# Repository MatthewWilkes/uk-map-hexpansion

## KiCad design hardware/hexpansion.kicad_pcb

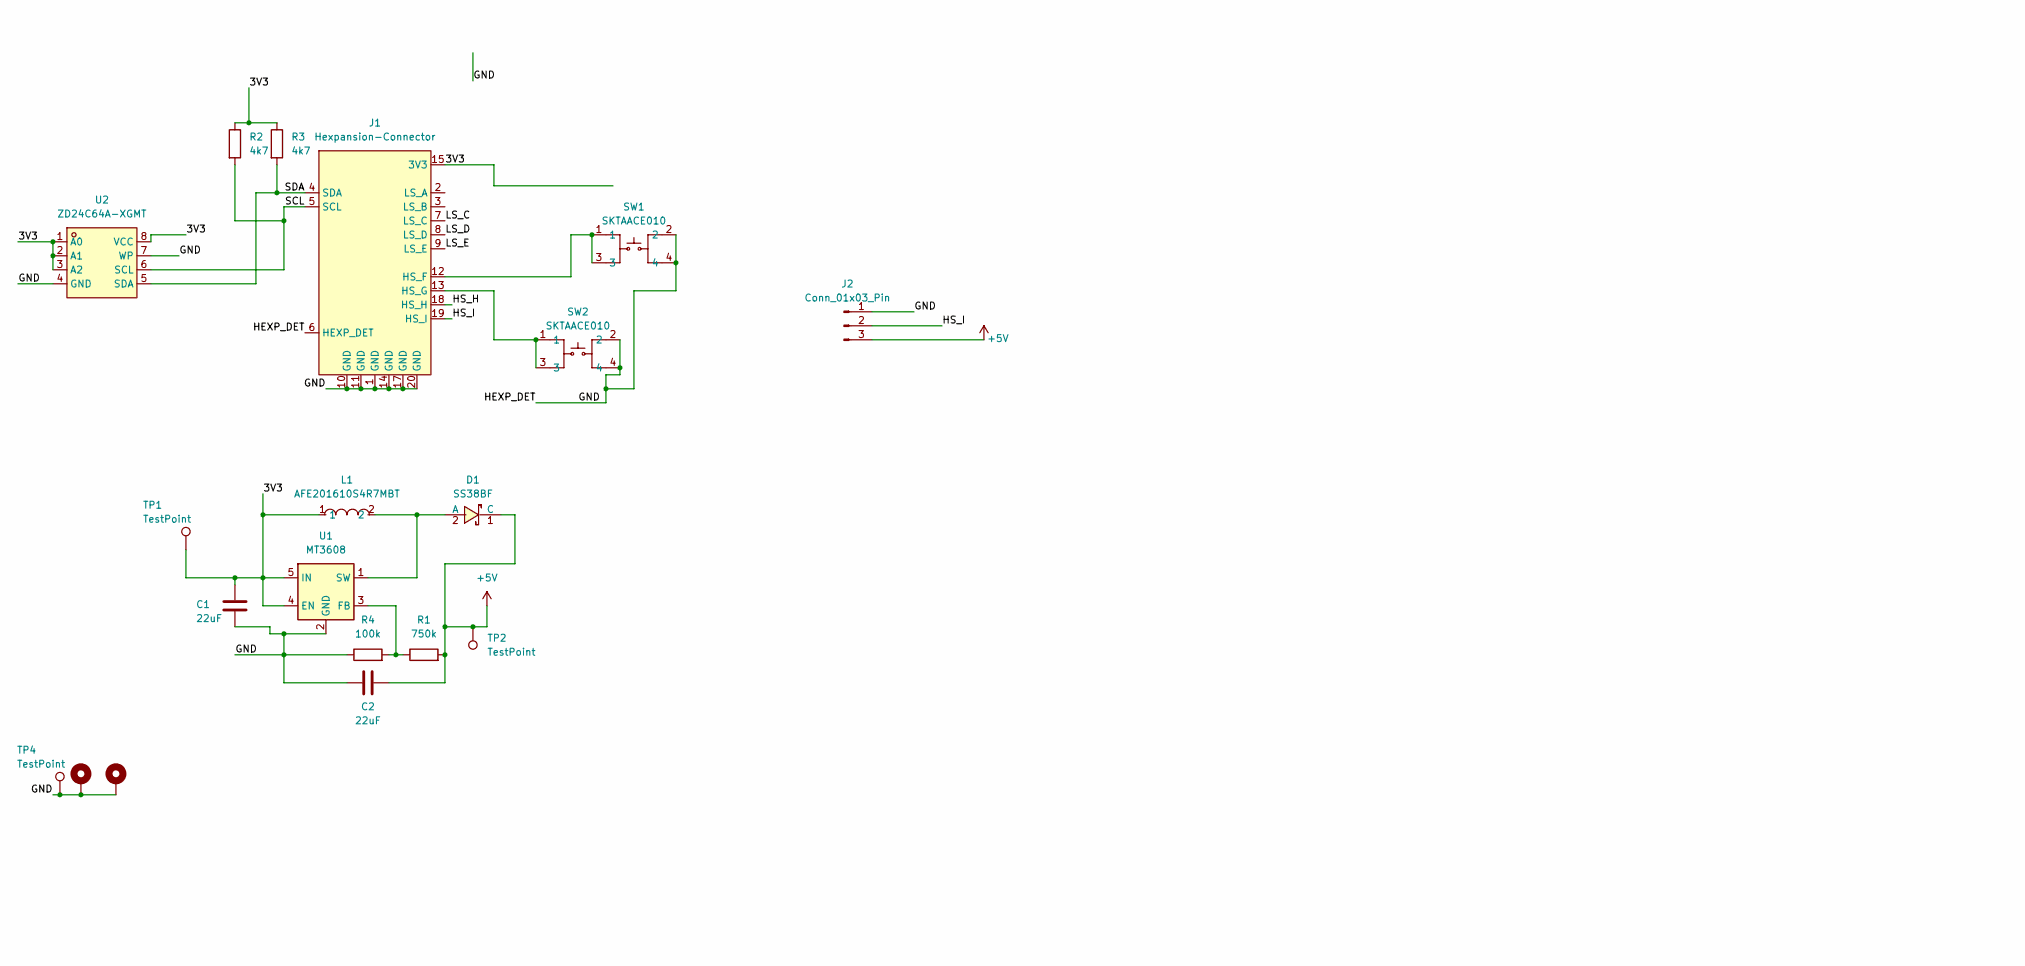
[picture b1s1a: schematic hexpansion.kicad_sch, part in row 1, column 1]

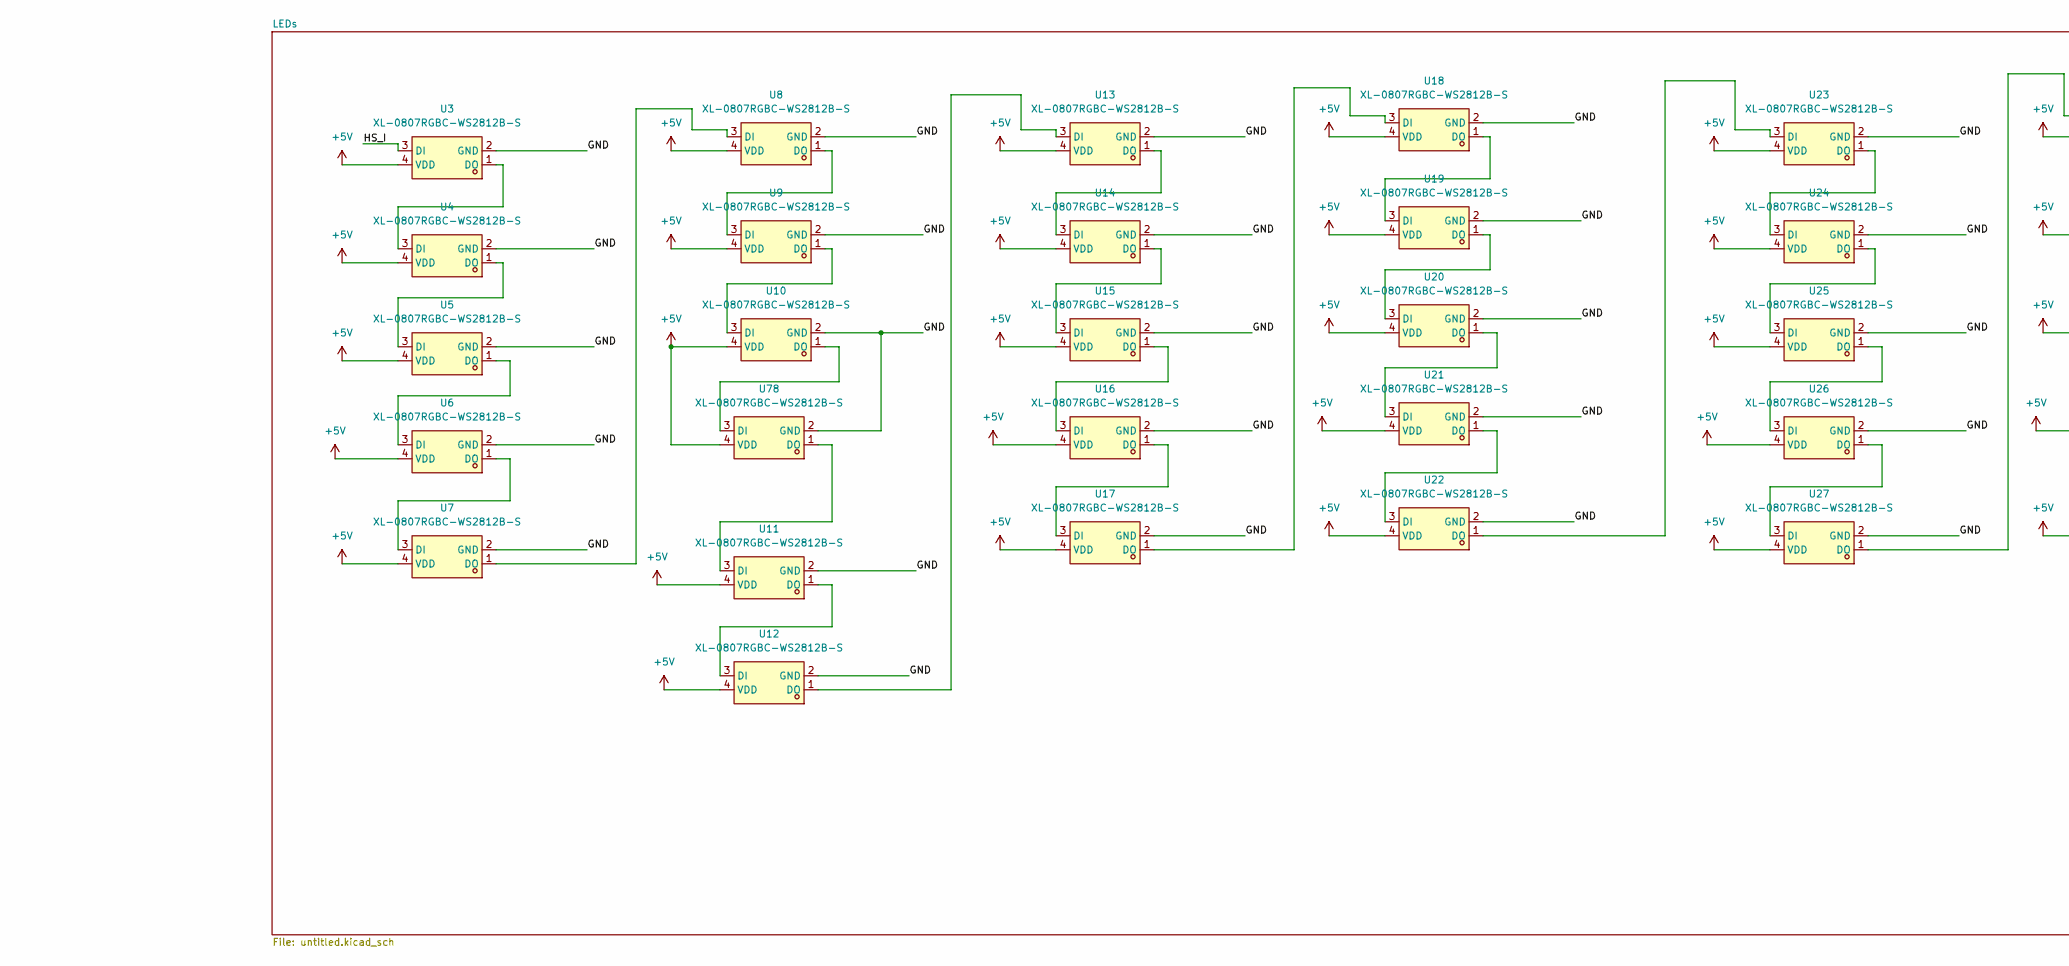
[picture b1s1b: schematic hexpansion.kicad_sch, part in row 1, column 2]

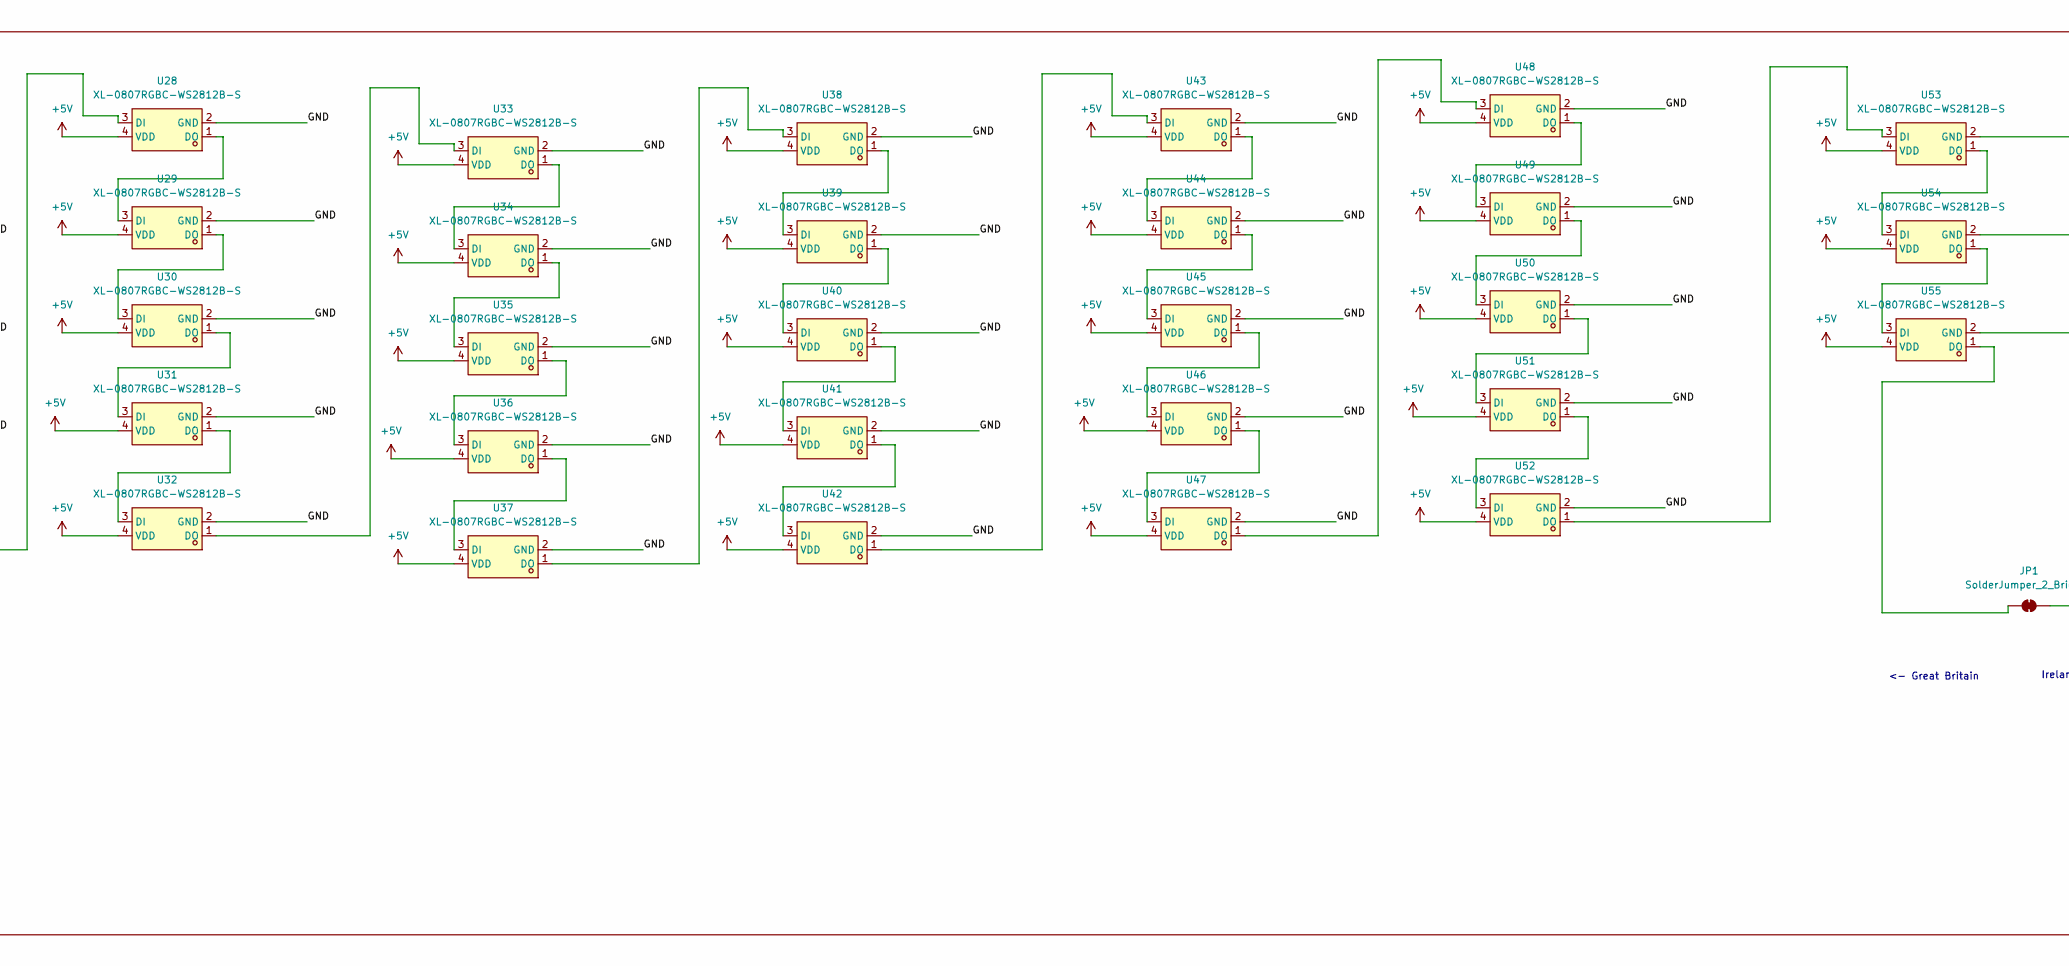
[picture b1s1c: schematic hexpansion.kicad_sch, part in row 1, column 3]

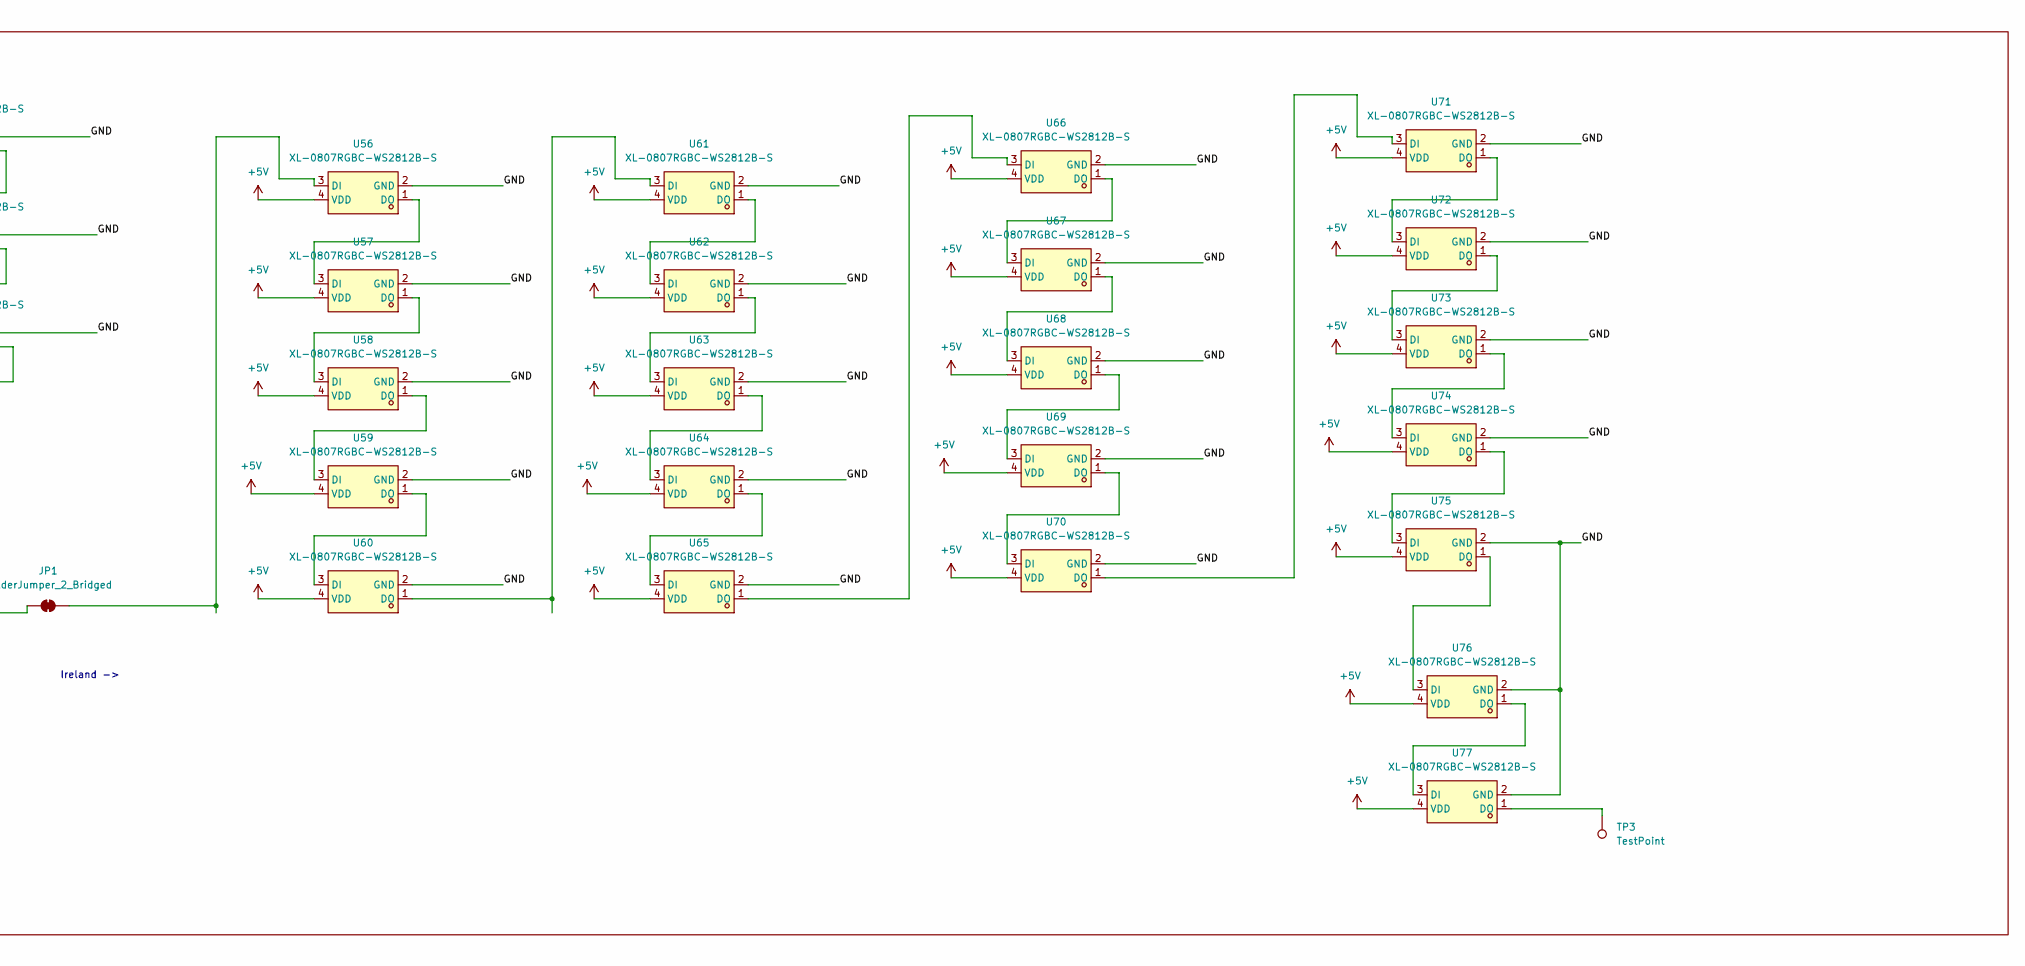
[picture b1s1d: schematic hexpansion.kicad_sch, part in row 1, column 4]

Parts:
C1, C2: 22uF; C_0603_1608Metric; LCSC Part C86295
D1: SS38BF; SMBF_L4.3-W3.6-LS5.3-RD; MPN SS38BF; LCSC Part C437976
H1, H2: MountingHole_Pad; MountingHole_2.2mm_M2_Pad_Via
J1: Hexpansion-Connector; hexpansion-edge-connector
J2: Conn_01x03_Pin; SolderWire-0.1sqmm_1x03_P3.6mm_D0.4mm_OD1mm
JP1: SolderJumper_2_Bridged; SolderJumper-2_P1.3mm_Bridged_RoundedPad1.0x1.5mm
L1: AFE201610S4R7MBT; IND-SMD_L2.0-W1.6; MPN AFE201610S4R7MBT; LCSC Part C22459317
R1: 750k; R_0603_1608Metric; LCSC Part C137684
R2, R3: 4k7; R_0603_1608Metric
R4: 100k; R_0603_1608Metric; LCSC Part C14675
SW1, SW2: SKTAACE010; KEY-SMD_4P-L2.6-W1.6-P0.80-LS3.0; MPN SKTAACE010; LCSC Part C358621
TP1, TP2, TP3, TP4: TestPoint; TestPoint_Pad_2.0x2.0mm
U1: MT3608; SOT-23-6; LCSC Part C84817
U2: ZD24C64A-XGMT; TSSOP-8_L4.4-W3.0-P0.65-LS6.4-BL; LCSC Part C2875852
U3, U4, U5, U6, U7, U8, U9, U10, U11, U12, U13, U14, U15, U16, U17, U18, U19, U20, U21, U22, U23, U24, U25, U26, U27, U28, U29, U30, U31, U32, U33, U34, U35, U36, U37, U38, U39, U40, U41, U42, U43, U44, U45, U46, U47, U48, U49, U50, U51, U52, U53, U54, U55, U56, U57, U58, U59, U60, U61, U62, U63, U64, U65, U66, U67, U68, U69, U70, U71, U72, U73, U74, U75, U76, U77, U78: XL-0807RGBC-WS2812B-S; LED-SMD_4P-L2.0-W1.8_XL-0807RGBC-WS2812B-S; LCSC Part C41413181

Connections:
+5V: C2.2, D1.1 (C), J2.3, R1.2, TP2.1, U3.4 (VDD), U4.4 (VDD), U5.4 (VDD), U6.4 (VDD), U7.4 (VDD), U8.4 (VDD), U9.4 (VDD), U10.4 (VDD), U11.4 (VDD), U12.4 (VDD), U13.4 (VDD), U14.4 (VDD), U15.4 (VDD), U16.4 (VDD), U17.4 (VDD), U18.4 (VDD), U19.4 (VDD), U20.4 (VDD), U21.4 (VDD), U22.4 (VDD), U23.4 (VDD), U24.4 (VDD), U25.4 (VDD), U26.4 (VDD), U27.4 (VDD), U28.4 (VDD), U29.4 (VDD), U30.4 (VDD), U31.4 (VDD), U32.4 (VDD), U33.4 (VDD), U34.4 (VDD), U35.4 (VDD), U36.4 (VDD), U37.4 (VDD), U38.4 (VDD), U39.4 (VDD), U40.4 (VDD), U41.4 (VDD), U42.4 (VDD), U43.4 (VDD), U44.4 (VDD), U45.4 (VDD), U46.4 (VDD), U47.4 (VDD), U48.4 (VDD), U49.4 (VDD), U50.4 (VDD), U51.4 (VDD), U52.4 (VDD), U53.4 (VDD), U54.4 (VDD), U55.4 (VDD), U56.4 (VDD), U57.4 (VDD), U58.4 (VDD), U59.4 (VDD), U60.4 (VDD), U61.4 (VDD), U62.4 (VDD), U63.4 (VDD), U64.4 (VDD), U65.4 (VDD), U66.4 (VDD), U67.4 (VDD), U68.4 (VDD), U69.4 (VDD), U70.4 (VDD), U71.4 (VDD), U72.4 (VDD), U73.4 (VDD), U74.4 (VDD), U75.4 (VDD), U76.4 (VDD), U77.4 (VDD), U78.4 (VDD); also elsewhere on the board
/3V3: C1.1, J1.15 (3V3), J1.16 (3V3), L1.1, R2.1, R3.1, TP1.1, U1.4 (EN), U1.5 (IN), U2.1 (A0), U2.2 (A1), U2.3 (A2), U2.8 (VCC); also elsewhere on the board
/GND: C1.2, C2.1, H1.1, H2.1, J1.1 (GND), J1.6 (HEXP_DET), J1.10 (GND), J1.11 (GND), J1.14 (GND), J1.17 (GND), J1.20 (GND), J2.1, R4.1, SW1.2, SW1.4, SW2.2, SW2.4, TP4.1, U1.2 (GND), U2.4 (GND), U2.7 (WP), U3.2 (GND), U4.2 (GND), U5.2 (GND), U6.2 (GND), U7.2 (GND), U8.2 (GND), U9.2 (GND), U10.2 (GND), U11.2 (GND), U12.2 (GND), U13.2 (GND), U14.2 (GND), U15.2 (GND), U16.2 (GND), U17.2 (GND), U18.2 (GND), U19.2 (GND), U20.2 (GND), U21.2 (GND), U22.2 (GND), U23.2 (GND), U24.2 (GND), U25.2 (GND), U26.2 (GND), U27.2 (GND), U28.2 (GND), U29.2 (GND), U30.2 (GND), U31.2 (GND), U32.2 (GND), U33.2 (GND), U34.2 (GND), U35.2 (GND), U36.2 (GND), U37.2 (GND), U38.2 (GND), U39.2 (GND), U40.2 (GND), U41.2 (GND), U42.2 (GND), U43.2 (GND), U44.2 (GND), U45.2 (GND), U46.2 (GND), U47.2 (GND), U48.2 (GND), U49.2 (GND), U50.2 (GND), U51.2 (GND), U52.2 (GND), U53.2 (GND), U54.2 (GND), U55.2 (GND), U56.2 (GND), U57.2 (GND), U58.2 (GND), U59.2 (GND), U60.2 (GND), U61.2 (GND), U62.2 (GND), U63.2 (GND), U64.2 (GND), U65.2 (GND), U66.2 (GND), U67.2 (GND), U68.2 (GND), U69.2 (GND), U70.2 (GND), U71.2 (GND), U72.2 (GND), U73.2 (GND), U74.2 (GND), U75.2 (GND), U76.2 (GND), U77.2 (GND), U78.2 (GND); also elsewhere on the board
/HS_H: J1.18 (HS_H)
/HS_I: J1.19 (HS_I), J2.2, U3.3 (DI); also elsewhere on the board
/LS_C: J1.7 (LS_C)
/LS_D: J1.8 (LS_D)
/LS_E: J1.9 (LS_E)
/SCL: J1.5 (SCL), R2.2, U2.6 (SCL)
/SDA: J1.4 (SDA), R3.2, U2.5 (SDA)
unnamed: D1.2 (A), L1.2, U1.1 (SW)
unnamed 11: J1.12 (HS_F), SW1.1, SW1.3; also elsewhere on the board
unnamed 12: J1.13 (HS_G), SW2.1, SW2.3; also elsewhere on the board
unnamed 13: JP1.1 (A), U55.1 (DO); also elsewhere on the board
unnamed 14: JP1.2 (B), U56.3 (DI); also elsewhere on the board
unnamed: R1.1, R4.2, U1.3 (FB)
unnamed: U3.1 (DO), U4.3 (DI)
unnamed: U4.1 (DO), U5.3 (DI)
unnamed: U5.1 (DO), U6.3 (DI)
unnamed: U6.1 (DO), U7.3 (DI)
unnamed: U7.1 (DO), U8.3 (DI)
unnamed: U8.1 (DO), U9.3 (DI)
unnamed: U9.1 (DO), U10.3 (DI)
unnamed: U10.1 (DO), U78.3 (DI)
unnamed: U11.3 (DI), U78.1 (DO)
unnamed: U11.1 (DO), U12.3 (DI)
unnamed: U12.1 (DO), U13.3 (DI)
unnamed: U13.1 (DO), U14.3 (DI)
unnamed: U14.1 (DO), U15.3 (DI)
unnamed: U15.1 (DO), U16.3 (DI)
unnamed: U16.1 (DO), U17.3 (DI)
unnamed: U17.1 (DO), U18.3 (DI)
unnamed: U18.1 (DO), U19.3 (DI)
unnamed: U19.1 (DO), U20.3 (DI)
unnamed: U20.1 (DO), U21.3 (DI)
unnamed: U21.1 (DO), U22.3 (DI)
unnamed: U22.1 (DO), U23.3 (DI)
unnamed: U23.1 (DO), U24.3 (DI)
unnamed: U24.1 (DO), U25.3 (DI)
unnamed: U25.1 (DO), U26.3 (DI)
unnamed: U26.1 (DO), U27.3 (DI)
unnamed: U27.1 (DO), U28.3 (DI)
unnamed: U28.1 (DO), U29.3 (DI)
unnamed: U29.1 (DO), U30.3 (DI)
unnamed: U30.1 (DO), U31.3 (DI)
unnamed: U31.1 (DO), U32.3 (DI)
unnamed: U32.1 (DO), U33.3 (DI)
unnamed: U33.1 (DO), U34.3 (DI)
unnamed: U34.1 (DO), U35.3 (DI)
unnamed: U35.1 (DO), U36.3 (DI)
unnamed: U36.1 (DO), U37.3 (DI)
unnamed: U37.1 (DO), U38.3 (DI)
unnamed: U38.1 (DO), U39.3 (DI)
unnamed: U39.1 (DO), U40.3 (DI)
unnamed: U40.1 (DO), U41.3 (DI)
unnamed: U41.1 (DO), U42.3 (DI)
unnamed: U42.1 (DO), U43.3 (DI)
unnamed: U43.1 (DO), U44.3 (DI)
unnamed: U44.1 (DO), U45.3 (DI)
unnamed: U45.1 (DO), U46.3 (DI)
unnamed: U46.1 (DO), U47.3 (DI)
unnamed: U47.1 (DO), U48.3 (DI)
unnamed: U48.1 (DO), U49.3 (DI)
unnamed: U49.1 (DO), U50.3 (DI)
unnamed: U50.1 (DO), U51.3 (DI)
unnamed: U51.1 (DO), U52.3 (DI)
unnamed: U52.1 (DO), U53.3 (DI)
unnamed: U53.1 (DO), U54.3 (DI)
unnamed: U54.1 (DO), U55.3 (DI)
unnamed: U56.1 (DO), U57.3 (DI)
unnamed: U57.1 (DO), U58.3 (DI)
unnamed: U58.1 (DO), U59.3 (DI)
unnamed: U59.1 (DO), U60.3 (DI)
unnamed: U60.1 (DO), U61.3 (DI)
unnamed: U61.1 (DO), U62.3 (DI)
unnamed: U62.1 (DO), U63.3 (DI)
unnamed: U63.1 (DO), U64.3 (DI)
unnamed: U64.1 (DO), U65.3 (DI)
unnamed: U65.1 (DO), U66.3 (DI)
unnamed: U66.1 (DO), U67.3 (DI)
unnamed: U67.1 (DO), U68.3 (DI)
unnamed: U68.1 (DO), U69.3 (DI)
unnamed: U69.1 (DO), U70.3 (DI)
unnamed: U70.1 (DO), U71.3 (DI)
unnamed: U71.1 (DO), U72.3 (DI)
unnamed: U72.1 (DO), U73.3 (DI)
unnamed: U73.1 (DO), U74.3 (DI)
unnamed: U74.1 (DO), U75.3 (DI)
unnamed: U75.1 (DO), U76.3 (DI)
unnamed: U76.1 (DO), U77.3 (DI)
unnamed 90: TP3.1, U77.1 (DO); also elsewhere on the board

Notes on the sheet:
<- Great Britain
Ireland ->

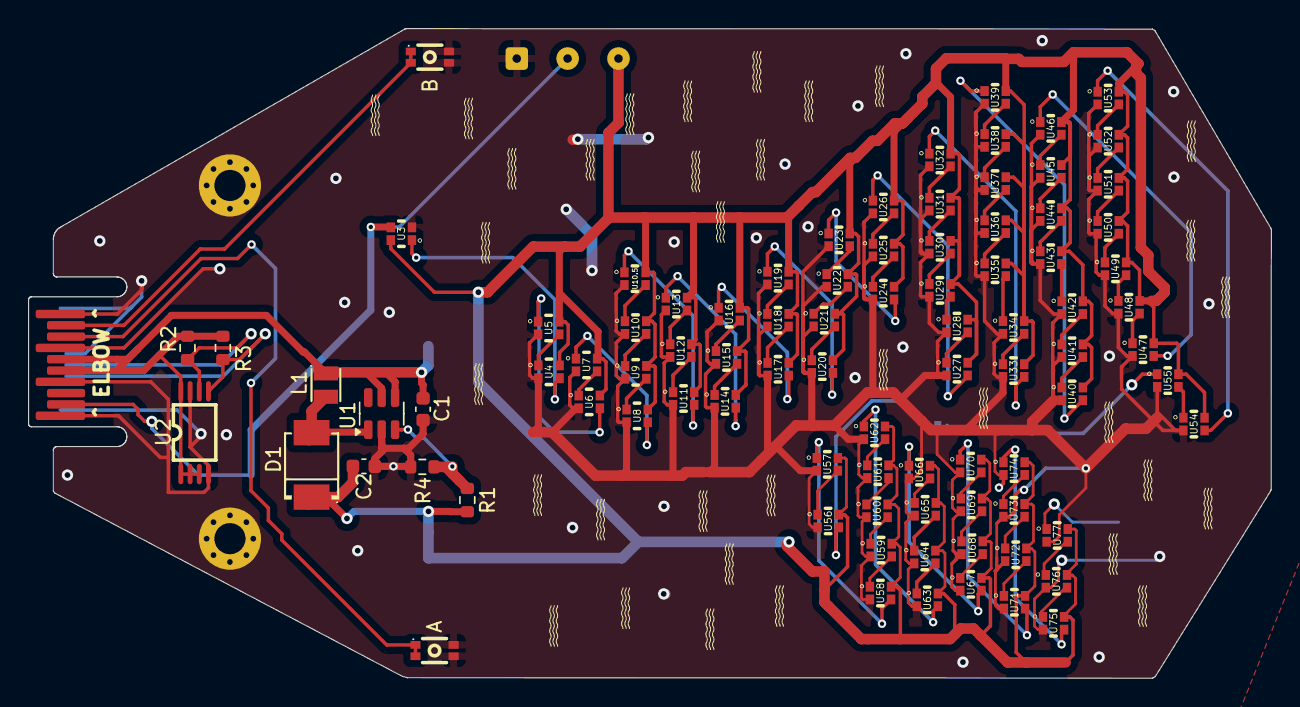
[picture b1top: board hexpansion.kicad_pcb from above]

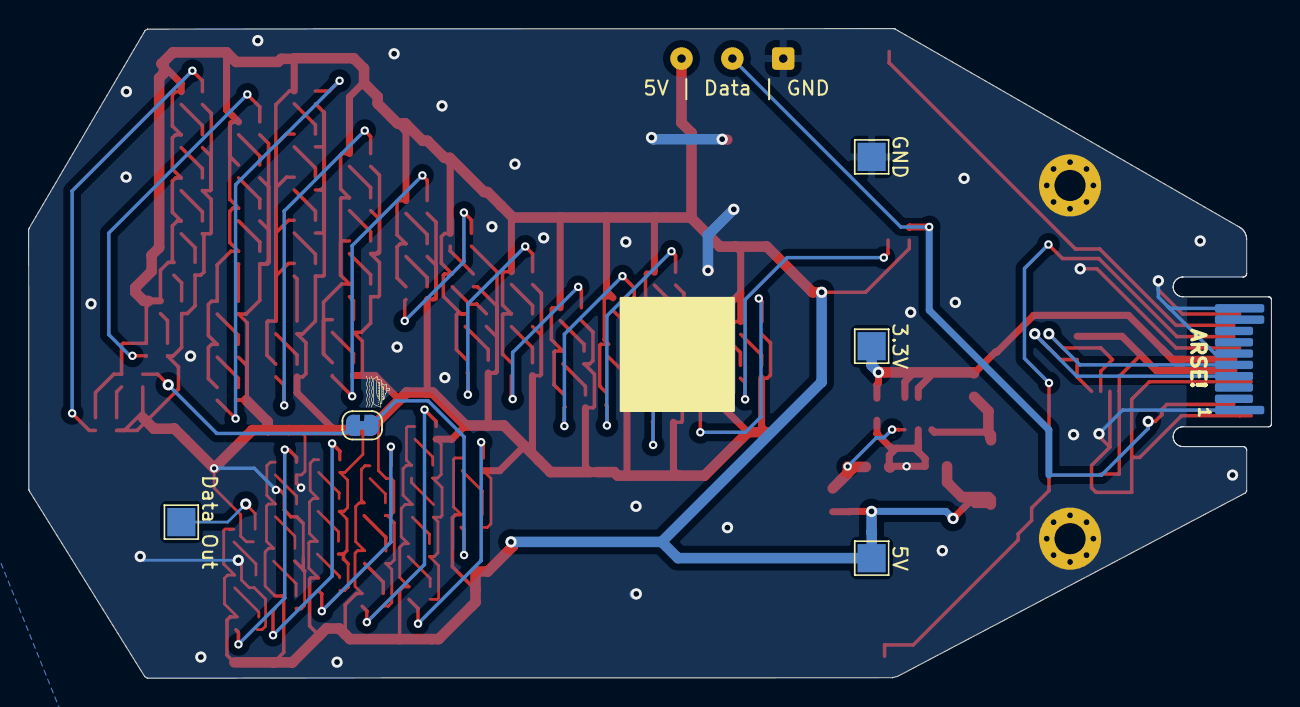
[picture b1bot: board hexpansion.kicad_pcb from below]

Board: 2 copper layers, 88.0 x 46.0 mm, 97 parts (6 on the bottom side), 87 nets.

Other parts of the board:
3.3V, 5V: TestPoint; TestPoint_Pad_2.0x2.0mm
5V | Data | GND: Conn_01x03_Pin; SolderWire-0.1sqmm_1x03_P3.6mm_D0.4mm_OD1mm
A: SKTAACE010; KEY-SMD_4P-L2.6-W1.6-P0.80-LS3.0
B: SKTAACE010; KEY-SMD_4P-L2.6-W1.6-P0.80-LS3.0
Data Out: TestPoint; TestPoint_Pad_2.0x2.0mm
GND: TestPoint; TestPoint_Pad_2.0x2.0mm
J1#2: SolderJumper_2_Bridged; SolderJumper-2_P1.3mm_Bridged_RoundedPad1.0x1.5mm

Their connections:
+5V: 5V.1, 5V | Data | GND.3; also elsewhere on the board
/3V3: 3.3V.1; also elsewhere on the board
/GND: 5V | Data | GND.1, A.2, A.4, B.2, B.4, GND.1; also elsewhere on the board
/HS_I: 5V | Data | GND.2; also elsewhere on the board
unnamed 11: B.1, B.3; also elsewhere on the board
unnamed 12: A.1, A.3; also elsewhere on the board
unnamed 13: J1#2.1 (A); also elsewhere on the board
unnamed 14: J1#2.2 (B); also elsewhere on the board
unnamed 90: Data Out.1; also elsewhere on the board

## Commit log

2026-04-05 First version
2026-04-19 Initial version
2026-04-19 Fix commit
2026-04-19 More moves
2026-04-19 Fully routed
2026-04-19 Improve decoupling of power supply
2026-04-19 Remove extraneous trace
2026-04-19 Add LCSC part numbers
2026-04-19 Update silkscreen and add some more ground ties
2026-04-19 Ready to fab
